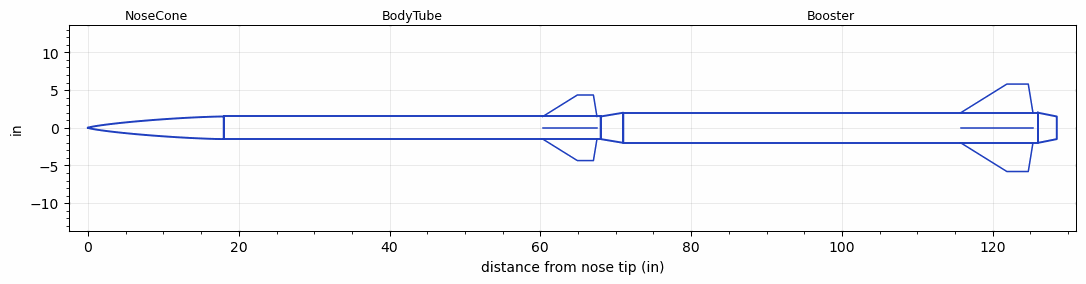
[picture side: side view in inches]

<RASAeroDocument>
 <FileVersion>2</FileVersion>
 <RocketDesign>
  <NoseCone>
   <Length>18</Length>
   <Diameter>3</Diameter>
   <Shape>Von Karman Ogive</Shape>
   <Location>0</Location>
  </NoseCone>
  <BodyTube>
   <Length>50</Length>
   <Diameter>3</Diameter>
   <Location>18</Location>
   <Fin>
    <Count>4</Count>
    <Chord>7.1775</Chord>
    <Span>2.85</Span>
    <SweepDistance>4.579</SweepDistance>
    <TipChord>2.13</TipChord>
    <Thickness>0.5</Thickness>
    <LERadius>0.08</LERadius>
    <Location>7.6725</Location>
    <AirfoilSection>Hexagonal</AirfoilSection>
    <FX1>0.5</FX1>
    <FX3>0.5</FX3>
   </Fin>
  </BodyTube>
  <Booster>
   <Length>55</Length>
   <Diameter>4</Diameter>
   <InsideDiameter>3</InsideDiameter>
   <Location>68</Location>
   <ShoulderLength>3</ShoulderLength>
   <BoattailLength>2.5</BoattailLength>
   <BoattailRearDiameter>3</BoattailRearDiameter>
   <Fin>
    <Count>4</Count>
    <Chord>9.57</Chord>
    <Span>3.8</Span>
    <SweepDistance>6.11</SweepDistance>
    <TipChord>2.84</TipChord>
    <Thickness>0.25</Thickness>
    <LERadius>0.08</LERadius>
    <Location>10.23</Location>
    <AirfoilSection>Hexagonal</AirfoilSection>
    <FX1>0.5</FX1>
    <FX3>0.5</FX3>
   </Fin>
  </Booster>
  <Surface>Smooth (Zero Roughness)</Surface>
  <ModifiedBarrowman>False</ModifiedBarrowman>
  <Turbulence>False</Turbulence>
  <UseBooster1>False</UseBooster1>
  <UseBooster2>False</UseBooster2>
 </RocketDesign>
 <LaunchSite>
  <Altitude>3000</Altitude>
  <Pressure>0</Pressure>
  <RodAngle>2</RodAngle>
  <RodLength>18</RodLength>
  <Temperature>85</Temperature>
  <WindSpeed>8</WindSpeed>
 </LaunchSite>
 <Recovery>
  <Altitude1>1000</Altitude1>
  <Altitude2>1000</Altitude2>
  <DeviceType1>None</DeviceType1>
  <DeviceType2>None</DeviceType2>
  <Event1>False</Event1>
  <Event2>False</Event2>
  <Size1>1</Size1>
  <Size2>1</Size2>
  <EventType1>None</EventType1>
  <EventType2>None</EventType2>
  <CD1>1.33</CD1>
  <CD2>1.33</CD2>
 </Recovery>
 <SimulationList>
  <Simulation>
   <SustainerEngine>EXS  (EX)</SustainerEngine>
   <SustainerLaunchWt>27.75</SustainerLaunchWt>
   <SustainerNozzleDiameter>2.5</SustainerNozzleDiameter>
   <SustainerCG>22.7</SustainerCG>
   <SustainerIgnitionDelay>15</SustainerIgnitionDelay>
   <Booster1Engine>EXB  (EX)</Booster1Engine>
   <Booster1LaunchWt>70.58</Booster1LaunchWt>
   <Booster1SeparationDelay>0</Booster1SeparationDelay>
   <Booster1IgnitionDelay>0</Booster1IgnitionDelay>
   <Booster1CG>57.01</Booster1CG>
   <Booster1NozzleDiameter>2.2</Booster1NozzleDiameter>
   <IncludeBooster1>True</IncludeBooster1>
   <Booster2Delay>0</Booster2Delay>
   <IncludeBooster2>False</IncludeBooster2>
   <TimetoApogee>62.94622</TimetoApogee>
   <MaxAltitude>45703.75</MaxAltitude>
   <MaxVelocity>2118.88</MaxVelocity>
  </Simulation>
 </SimulationList>
</RASAeroDocument>
